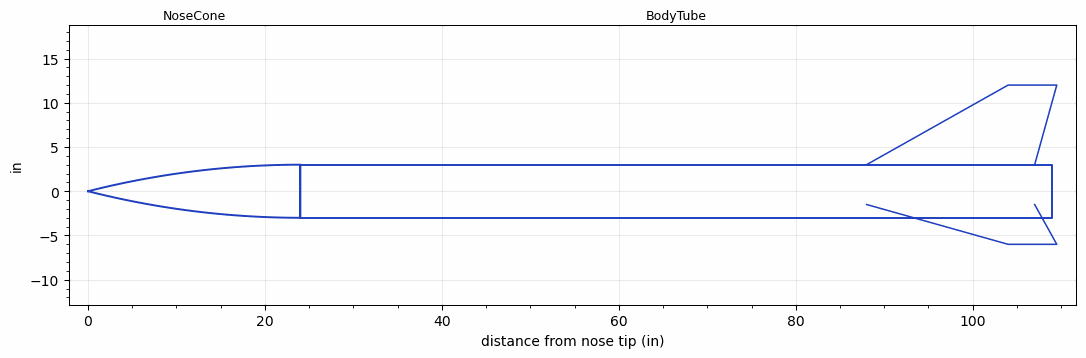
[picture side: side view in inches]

<RASAeroDocument>
 <FileVersion>2</FileVersion>
 <RocketDesign>
  <NoseCone>
   <Length>24</Length>
   <Diameter>6</Diameter>
   <Shape>Tangent Ogive</Shape>
   <Location>0</Location>
  </NoseCone>
  <BodyTube>
   <Length>85</Length>
   <Diameter>6</Diameter>
   <RailGuideDiameter>0.5</RailGuideDiameter>
   <RailGuideHeight>0.5</RailGuideHeight>
   <Location>24</Location>
   <Fin>
    <Count>3</Count>
    <Chord>19</Chord>
    <Span>9</Span>
    <SweepDistance>16</SweepDistance>
    <TipChord>5.5</TipChord>
    <Thickness>0.375</Thickness>
    <Location>21</Location>
    <AirfoilSection>Rounded</AirfoilSection>
    <FX1>1</FX1>
    <FX3>0.5</FX3>
   </Fin>
  </BodyTube>
  <Surface>Smooth (Zero Roughness)</Surface>
  <ModifiedBarrowman>False</ModifiedBarrowman>
  <Turbulence>False</Turbulence>
  <UseBooster1>False</UseBooster1>
  <UseBooster2>False</UseBooster2>
  <Comments>Cancer Descending - Corky Borgman
LDRS-26; Jean Dry Lake

Two Barometric Altimeters
Transolve 6400 ft
Olsen 5975 ft
Average of Two Barometric Altimeters = 6188 ft

RASAero Prediction = 6328 ft
Error = 2.26%
</Comments>
 </RocketDesign>
 <LaunchSite>
  <Altitude>2750</Altitude>
  <Pressure>0</Pressure>
  <RodAngle>0</RodAngle>
  <RodLength>10</RodLength>
  <Temperature>100</Temperature>
  <WindSpeed>0</WindSpeed>
 </LaunchSite>
 <Recovery>
  <Altitude1>1000</Altitude1>
  <Altitude2>1000</Altitude2>
  <DeviceType1>None</DeviceType1>
  <DeviceType2>None</DeviceType2>
  <Event1>False</Event1>
  <Event2>False</Event2>
  <Size1>1</Size1>
  <Size2>1</Size2>
  <EventType1>None</EventType1>
  <EventType2>None</EventType2>
  <CD1>1.33</CD1>
  <CD2>1.33</CD2>
 </Recovery>
 <SimulationList>
  <Simulation>
   <SustainerEngine>M1297W  (AT)</SustainerEngine>
   <SustainerLaunchWt>49.84</SustainerLaunchWt>
   <SustainerCG>74</SustainerCG>
   <SustainerIgnitionDelay>0</SustainerIgnitionDelay>
   <Booster1SeparationDelay>0</Booster1SeparationDelay>
   <Booster1IgnitionDelay>0</Booster1IgnitionDelay>
   <IncludeBooster1>False</IncludeBooster1>
   <Booster2Delay>0</Booster2Delay>
   <IncludeBooster2>False</IncludeBooster2>
   <TimetoApogee>20.35037</TimetoApogee>
   <MaxAltitude>6327.609</MaxAltitude>
   <MaxVelocity>648.6934</MaxVelocity>
  </Simulation>
 </SimulationList>
</RASAeroDocument>
